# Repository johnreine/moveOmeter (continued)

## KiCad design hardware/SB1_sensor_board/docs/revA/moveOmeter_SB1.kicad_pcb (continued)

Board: 4 copper layers, 112 parts (52 on the bottom side), 66 nets, no tracks yet.

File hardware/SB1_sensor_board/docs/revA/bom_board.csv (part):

Refs,Qty per board,Value,Manufacturer,MPN,Footprint,Fit,Vendor Part #,"Price (qty 1, USD)",Ext price per board (USD),Vendor Link,Datasheet
"C1, C6",2,10nF 50V X7R,KEMET,C1206C103K5RACTU,C_1206_3216Metric_Pad1.33x1.80mm_HandSolder,,399-C1206C103K5RACTUCT-ND,0.22,0.44,https://www.digikey.com/en/products/detail/kemet/C1206C103K5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,https://www.yageogroup.com/content/datasheet/asset/file/KEM_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
"C2, C4, C5, C7, C9, C10, C15, C17, C21, C22, C23, C24, C26, C29, C30, C31, C32",17,100nF 50V X7R,Samsung,CL31B104KBCNNNC,C_1206_3216Metric_Pad1.33x1.80mm_HandSolder,,1276-1017-1-ND,0.15,2.55,https://www.digikey.com/en/products/detail/samsung-electro-m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,https://weblib.samsungsem.com/mlcc/mlcc-ec-data-sheet.do?par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
"C3, C8, C11, C12",4,1uF 50V X7R,Yageo,CC1206KKX7R9BB105,C_1206_3216Metric_Pad1.33x1.80mm_HandSolder,,311-1963-1-ND,0.36,1.44,https://www.digikey.com/en/products/detail/yageo/CC1206KKX7R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,https://yageogroup.com/content/datasheet/asset/file/UPY-GPHC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
"C13, C14, C16, C25, C28",5,10uF 25V X7R,Murata,GRM32DR71E106KA12L,C_1210_3225Metric_Pad1.33x2.70mm_HandSolder,,490-1867-1-ND,0.93,4.65,https://www.digikey.com/en/products/detail/murata-electronic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,https://pim.murata.com/asset/pim4/ceramicCapacitorSMD/GRM32D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
C18,1,6.8pF C0G,Yageo,CC1206CRNPO9BN6R8,C_1206_3216Metric_Pad1.33x1.80mm_HandSolder,,311-4367-1-ND,0.31,0.31,https://www.digikey.com/en/products/detail/yageo/CC1206CRNPO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,https://yageogroup.com/download/specsheet/CC1206CRNPO9BN6R8
"C19, C20",2,22uF 25V X5R,Murata,GRM32ER61E226KE15L,C_1210_3225Metric_Pad1.33x2.70mm_HandSolder,,490-3889-1-ND,2.21,4.42,https://www.digikey.com/en/products/detail/murata-electronic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,https://www.mouser.com/datasheet/2/281/1/GRM32ER61E226KE15_0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
C27,1,100uF 16V polymer,KEMET,A759EK107M1CAAE018,CP_Radial_D6.3mm_P2.50mm,,399-A759EK107M1CAAE018-ND,0.59,0.59,https://www.digikey.com/en/products/result?keywords=399-A759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,https://www.mouser.com/datasheet/2/447/KEM_A4072_A759-3316694.pdf
D1,1,BAT54C,onsemi,BAT54CLT1G,SOT-23,,BAT54CLT1GOSCT-ND,0.14,0.14,https://www.digikey.com/en/products/result?keywords=BAT54CLT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,https://www.onsemi.com/pdf/datasheet/bat54lt1-d.pdf
"D2, D3, D4",3,green,Lite-On,LTST-C150GKT,LED_1206_3216Metric_Pad1.42x1.75mm_HandSolder,,160-1169-1-ND,0.21,0.63,https://www.digikey.com/en/products/detail/liteon/LTST-C150G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,https://www.mouser.com/datasheet/2/239/Lite_On_LTST_C150GKT-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
"FB1, FB2",2,220R@100MHz 4A,Taiyo Yuden,LSMGA321616T221NG,L_1206_3216Metric_Pad1.22x1.90mm_HandSolder,,587-LSMGA321616T221NGCT-ND,0.32,0.64,https://www.digikey.com/en/products/detail/taiyo-yuden/LSMGA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,https://mm.digikey.com/Volume0/opasdata/d220001/medias/docus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
"J1, J2",2,USB4105-GF-A,GCT,USB4105-GF-A,USB_C_Receptacle_GCT_USB4105-xx-A_16P_TopMnt_Horizontal,,2073-USB4105-GF-ACT-ND,0.80,1.6,https://www.digikey.com/en/products/detail/gct/USB4105-GF-A/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,https://gct.co/download?type=PDFDrawing&name=USB4105.pdf
J3,1,Mainboard link,Sullins,SBH11-PBPC-D10-ST-BK,IDC-Header_2x10_P2.54mm_Vertical,,S9172-ND,0.46,0.46,https://www.digikey.com/en/products/result?keywords=S9172-ND,https://www.futureelectronics.com/p/2009022
J4,1,HLK-LD6004 on board,Sullins,LPPB051NFFN-RC,HLK-LD6004_Module_2x1x05_P1.27mm,,S9008E-05-ND,0.93,0.93,https://www.digikey.com/en/products/detail/sullins-connector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,https://s3.amazonaws.com/catalogspreads-pdf/PAGE96-97%20.050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
J5,1,HLK-LD2450 on board,Sullins,NPPN042AFCN-RC,HLK-LD2450_Module_2x04_P2.00mm,,S5750-04-ND,1.04,1.04,https://www.digikey.com/en/products/detail/sullins-connector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,https://drawings-pdf.s3.amazonaws.com/10497.pdf
L1,1,2.2uH Isat>2A,Bourns,SRN4018-2R2M,L_Bourns-SRN4018,,SRN4018-2R2MCT-ND,0.40,0.4,https://www.digikey.com/en/products/detail/bourns-inc/SRN401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,https://www.bourns.com/docs/Product-Datasheets/SRN4018.pdf
"Q1, Q3",2,2N7002,onsemi,2N7002LT1G,SOT-23,,2N7002LT1GOSCT-ND,0.25,0.5,https://www.digikey.com/en/products/detail/onsemi/2N7002LT1G/918297,https://www.onsemi.com/pdf/datasheet/2n7002l-d.pdf
"Q2, Q4",2,AO3400A,Alpha & Omega,AO3400A,SOT-23,,785-1000-1-ND,0.52,1.04,https://www.digikey.com/en/products/detail/alpha-omega-semic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,https://www.aosmd.com/res/datasheets/AO3400A.pdf
"R1, R2, R7, R8",4,5.1k,Yageo,RC1206FR-075K1L,R_1206_3216Metric_Pad1.30x1.75mm_HandSolder,,311-5.10KFRCT-ND,0.11,0.44,https://www.digikey.com/en/products/detail/yageo/RC1206FR-07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,https://yageogroup.com/content/datasheet/asset/file/PYU-RC_G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
"R3, R9",2,1M,Yageo,RC1206FR-071ML,R_1206_3216Metric_Pad1.30x1.75mm_HandSolder,,311-1.00MFRCT-ND,0.10,0.2,https://www.digikey.com/en/products/detail/yageo/RC1206FR-07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,https://yageogroup.com/content/datasheet/asset/file/PYU-RC_G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
"R4, R10",2,499,Yageo,RC1206FR-07499RL,R_1206_3216Metric_Pad1.30x1.75mm_HandSolder,,311-499FRCT-ND,0.10,0.2,https://www.digikey.com/en/products/detail/yageo/RC1206FR-07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,https://yageogroup.com/content/datasheet/asset/file/PYU-RC_G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
"R5, R16, R24, R25, R35",5,100k,Yageo,RC1206FR-07100KL,R_1206_3216Metric_Pad1.30x1.75mm_HandSolder,,311-100KFRCT-ND,0.10,0.5,https://www.digikey.com/en/products/detail/yageo/RC1206FR-07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,https://yageogroup.com/content/datasheet/asset/file/PYU-RC_G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
R6,1,27k,Yageo,RC1206FR-0727KL,R_1206_3216Metric_Pad1.30x1.75mm_HandSolder,,311-27.0KFRCT-ND,0.10,0.1,https://www.digikey.com/en/products/detail/yageo/RC1206FR-07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,https://yageogroup.com/content/datasheet/asset/file/PYU-RC_G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
"R11, R17, R19, R20, R21, R22, R23, R31, R32, R33",10,1k,Yageo,RC1206FR-071KL,R_1206_3216Metric_Pad1.30x1.75mm_HandSolder,,311-1.00KFRCT-ND,0.10,1.0,https://www.digikey.com/en/products/detail/yageo/RC1206FR-07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,https://yageogroup.com/content/datasheet/asset/file/PYU-RC_G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
"R12, R13, R14, R28, R34",5,10k,Yageo,RC1206FR-0710KL,R_1206_3216Metric_Pad1.30x1.75mm_HandSolder,,311-10.0KFRCT-ND,0.10,0.5,https://www.digikey.com/en/products/detail/yageo/RC1206FR-07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,https://yageogroup.com/content/datasheet/asset/file/PYU-RC_G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
R15,1,453k,Yageo,RC1206FR-07453KL,R_1206_3216Metric_Pad1.30x1.75mm_HandSolder,,311-453KFRCT-ND,0.10,0.1,https://www.digikey.com/en/products/detail/yageo/RC1206FR-07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,https://yageogroup.com/content/datasheet/asset/file/PYU-RC_G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
R18,1,50mΩ 1%,Vishay,WSL1206R0500FEA,R_1206_3216Metric_Pad1.30x1.75mm_HandSolder,,WSLC-.05CT-ND,0.93,0.93,https://www.digikey.com/en/products/detail/vishay-dale/WSL12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,https://www.vishay.com/docs/30100/wsl.pdf
"R26, R36",2,4.7k,Yageo,RC1206FR-074K7L,R_1206_3216Metric_Pad1.30x1.75mm_HandSolder,,311-4.70KFRCT-ND,0.10,0.2,https://www.digikey.com/en/products/detail/yageo/RC1206FR-07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,https://yageogroup.com/content/datasheet/asset/file/PYU-RC_G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
"R27, R37",2,10,Yageo,RC1206FR-0710RL,R_1206_3216Metric_Pad1.30x1.75mm_HandSolder,,311-10.0FRCT-ND,0.16,0.32,https://www.digikey.com/en/products/detail/yageo/RC1206FR-07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,https://yageogroup.com/content/datasheet/asset/file/PYU-RC_G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
R29,1,2.2k,Yageo,RC1206FR-072K2L,R_1206_3216Metric_Pad1.30x1.75mm_HandSolder,,311-2.20KFRCT-ND,0.10,0.1,https://www.digikey.com/en/products/detail/yageo/RC1206FR-07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,https://yageogroup.com/content/datasheet/asset/file/PYU-RC_G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
R30,1,100mΩ 1%,Vishay,WSL1206R1000FEA,R_1206_3216Metric_Pad1.30x1.75mm_HandSolder,,WSLC-.10CT-ND,0.65,0.65,https://www.digikey.com/en/products/detail/vishay-dale/WSL12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,https://www.vishay.com/docs/30100/wsl.pdf
TP1,1,3V3,Keystone,5000,TestPoint_Keystone_5000-5004_Miniature,,36-5000-ND,0.35,0.35,https://www.digikey.com/en/products/detail/keystone-electron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,https://www.keyelco.com/userAssets/file/K75p62.pdf
TP2,1,GND,Keystone,5001,TestPoint_Keystone_5000-5004_Miniature,,36-5001-ND,0.27,0.27,https://www.digikey.com/en/products/detail/keystone-electron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,https://www.keyelco.com/userAssets/file/K75p62.pdf
TP3,1,5V_RIB,Keystone,5000,TestPoint_Keystone_5000-5004_Miniature,,36-5000-ND,0.35,0.35,https://www.digikey.com/en/products/detail/keystone-electron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,https://www.keyelco.com/userAssets/file/K75p62.pdf
TP4,1,A_3V3,Keystone,5000,TestPoint_Keystone_5000-5004_Miniature,,36-5000-ND,0.35,0.35,https://www.digikey.com/en/products/detail/keystone-electron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,https://www.keyelco.com/userAssets/file/K75p62.pdf
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
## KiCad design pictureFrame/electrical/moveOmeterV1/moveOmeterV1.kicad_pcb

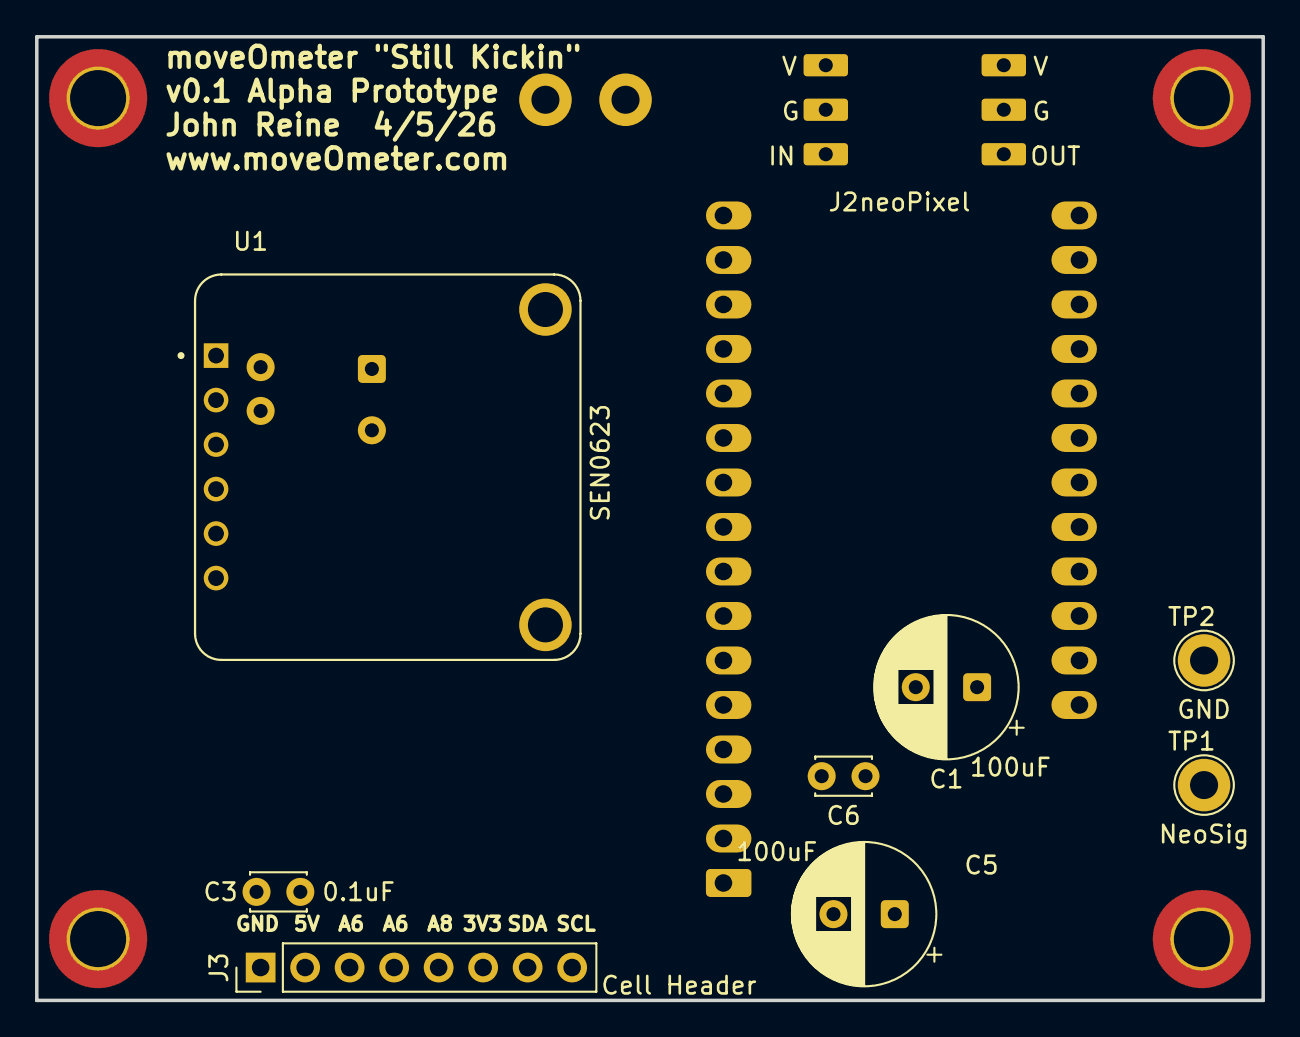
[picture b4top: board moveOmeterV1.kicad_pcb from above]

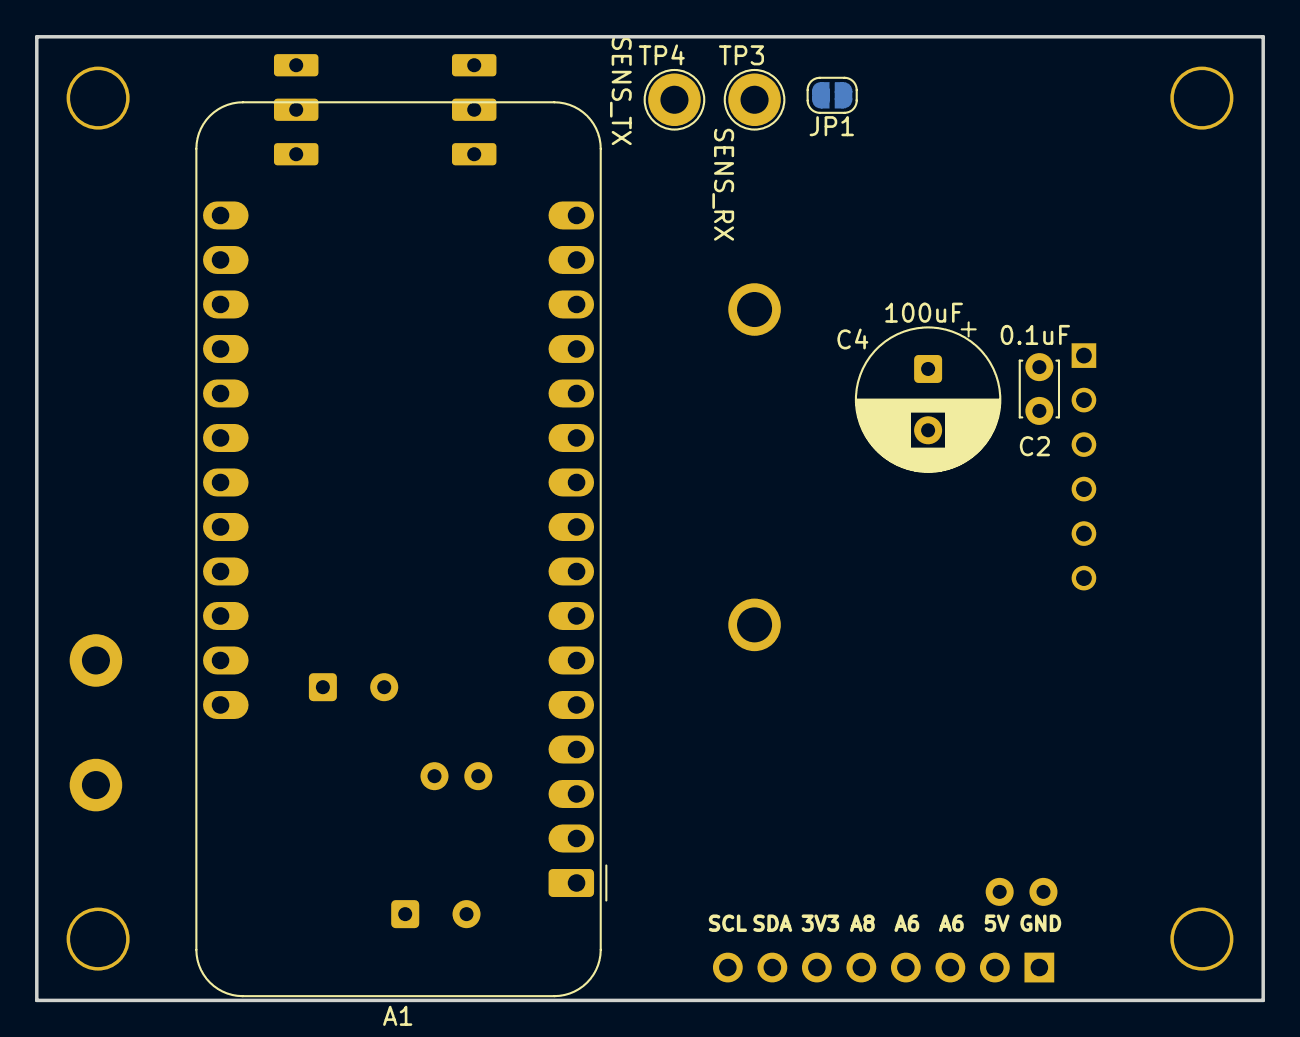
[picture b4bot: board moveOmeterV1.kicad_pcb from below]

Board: 2 copper layers, 70.0 x 55.0 mm, 15 parts (6 on the bottom side), 13 nets, no tracks yet.

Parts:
A1: Adafruit_Feather_ESP32-C6; Adafruit_Feather
C1, C4, C5: 100uF; CP_Radial_D8.0mm_P3.50mm
C2, C3, C6: 0.1uF; C_Disc_D3.0mm_W2.0mm_P2.50mm
J2: neoPixel; neoPixel6pin
J3: Cell Header; PinHeader_1x08_P2.54mm_Vertical
JP1: SolderJumper_2_Open; SolderJumper-2_P1.3mm_Open_RoundedPad1.0x1.5mm
TP1: NeoSig; TestPoint_Loop_D2.60mm_Drill1.6mm_Beaded
TP2: GND; TestPoint_Loop_D2.60mm_Drill1.6mm_Beaded
TP3: SENS_RX; TestPoint_Loop_D2.60mm_Drill1.6mm_Beaded
TP4: SENS_TX; TestPoint_Loop_D2.60mm_Drill1.6mm_Beaded
U1: SEN0623; MODULE_SEN0623

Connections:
+3V3 500mA: A1.2 (3V3), J2.1, J3.6
/5V_USB: A1.26 (USB), C1.1, C2.1, C3.1, C4.1, C5.1, C6.1, J3.2, U1.1 (VIN)
/A3: A1.8 (I39/A3), J2.3, TP1.1
/A6: A1.19 (A6/IO14), J3.4
/A7: A1.20 (A7/IO32), J3.3
/A8: A1.21 (A8/IO15), J3.5
/A9: A1.22 (A9/IO33), U1.6 (IO2)
/SCL: A1.6 (DAC1/A1), J3.8
/SDA: A1.7 (I34/A2), J3.7
/SENS_RX: A1.14 (RX/IO16), TP3.1, U1.4 (TX)
/SENS_TX: A1.15 (TX/IO17), TP4.1, U1.3 (RX)
GND: A1.4 (GND), C1.2, C2.2, C3.2, C4.2, C5.2, C6.2, J2.2, J3.1, JP1.1 (A), TP2.1, U1.2 (GND)
unnamed: A1.5 (DAC2/A0), U1.5 (IO1)
